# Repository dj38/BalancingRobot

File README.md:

# BalancingRobot
Balancing robot based on STM32F4 microcontroller

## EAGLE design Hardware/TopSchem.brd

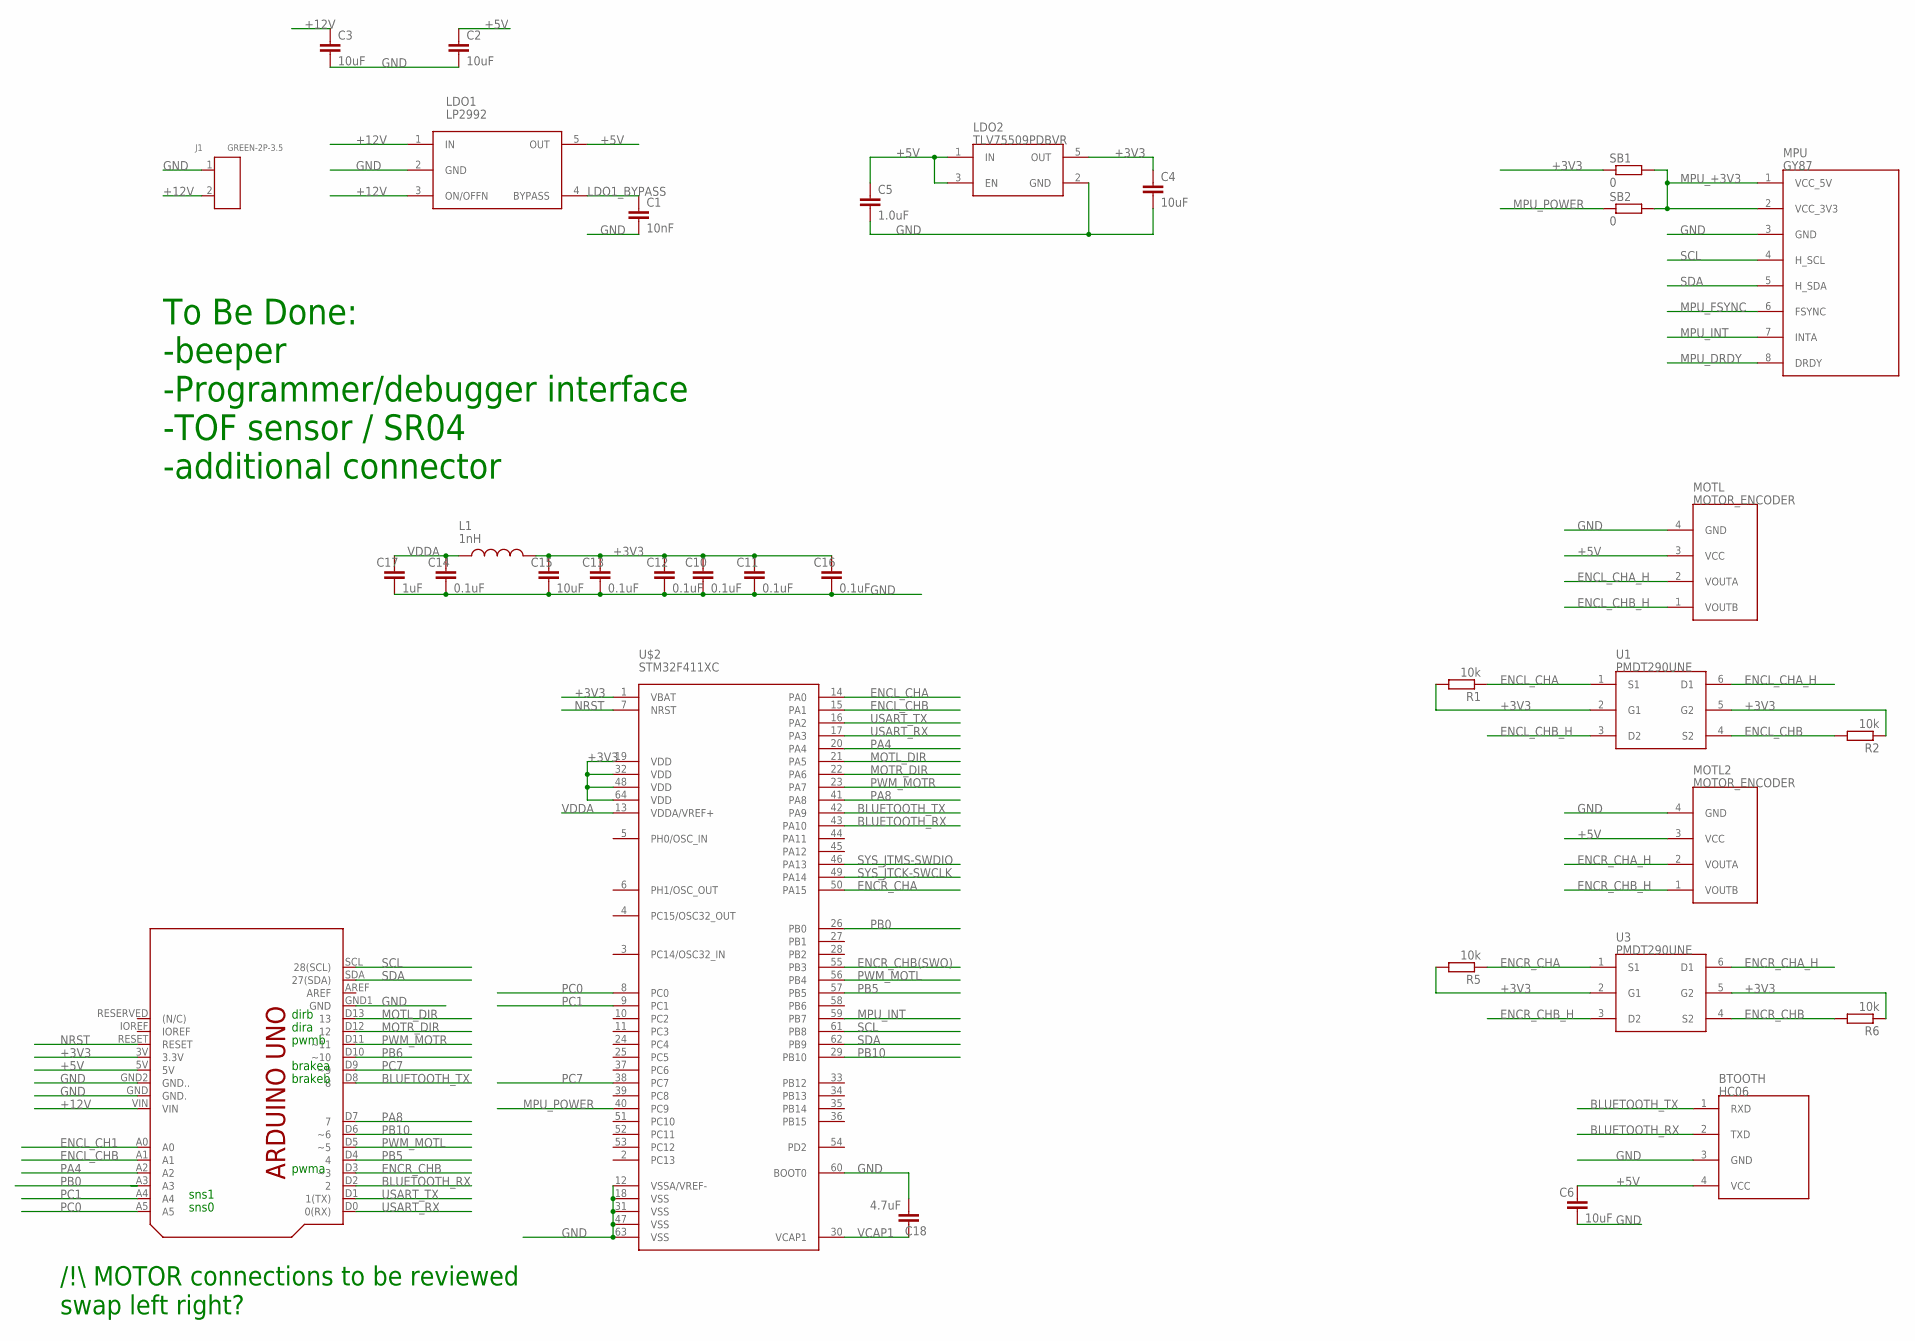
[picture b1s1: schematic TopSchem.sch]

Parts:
BTOOTH: HC06
C1: 10nF; 0603
C2, C3, C4, C6, C15: 10uF; 0603
C5: 1.0uF; 0603
C10, C11, C12, C13, C14, C16: 0.1uF; 0603
C17: 1uF; 0603
C18: 4.7uF; 0603
J1: GREEN-2P-3.5; H2-3.5-7.0X7.0MM
L1: 1nH; C0603
LDO1: LP2992; WE-TVS_SOT23-5L
LDO2: TLV75509PDBVR; WE-TVS_SOT23-5L
MOTL, MOTL2: MOTOR_ENCODER; ENCODER
MPU: GY87; SIP8
R1, R2, R5, R6: 10k; R0603
SB1, SB2: 0; R0603
SHIELD: ARDUINO_UNO_EXTARDUINO_R3; ARDUINOR3
U1, U3: PMDT290UNE; SOT666
U$2: STM32F411XC; LQFP64

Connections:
+3V3: C4.1, C10.1, C11.1, C12.1, C13.1, C15.1, C16.1, L1.2, LDO2.5 (OUT), R1.2, R2.1, R5.2, R6.1, SB1.1, SHIELD.3V (3.3V), U1.2 (G1), U1.5 (G2), U3.2 (G1), U3.5 (G2), U$2.1 (VBAT), U$2.19 (VDD), U$2.32 (VDD), U$2.48 (VDD), U$2.64 (VDD)
+5V: BTOOTH.4 (VCC), C2.1, C5.1, C6.1, LDO1.5 (OUT), LDO2.1 (IN), LDO2.3 (EN), MOTL.3 (VCC), MOTL2.3 (VCC), SHIELD.5V
+12V: C3.1, J1.2, LDO1.1 (IN), LDO1.3 (ON/OFFN), SHIELD.VIN
BLUETOOTH_RX: BTOOTH.2 (TXD), SHIELD.D2 (2), U$2.43 (PA10)
BLUETOOTH_TX: BTOOTH.1 (RXD), SHIELD.D8 (8), U$2.42 (PA9)
ENCL_CH1: SHIELD.A0
ENCL_CHA: R1.1, U1.1 (S1), U$2.14 (PA0)
ENCL_CHA_H: MOTL.2 (VOUTA), U1.6 (D1)
ENCL_CHB: R2.2, SHIELD.A1, U1.4 (S2), U$2.15 (PA1)
ENCL_CHB_H: MOTL.1 (VOUTB), U1.3 (D2)
ENCR_CHA: R5.1, U3.1 (S1), U$2.50 (PA15)
ENCR_CHA_H: MOTL2.2 (VOUTA), U3.6 (D1)
ENCR_CHB: R6.2, SHIELD.D3 (~3), U3.4 (S2)
ENCR_CHB(SWO): U$2.55 (PB3)
ENCR_CHB_H: MOTL2.1 (VOUTB), U3.3 (D2)
GND: BTOOTH.3 (GND), C1.2, C2.2, C3.2, C4.2, C5.2, C6.2, C10.2, C11.2, C12.2, C13.2, C14.2, C15.2, C16.2, C17.2, C18.2, J1.1, LDO1.2 (GND), LDO2.2 (GND), MOTL.4 (GND), MOTL2.4 (GND), MPU.3 (GND), SHIELD.GND (GND.), SHIELD.GND1 (GND), SHIELD.GND2 (GND..), U$2.12 (VSSA/VREF-), U$2.18 (VSS), U$2.31 (VSS), U$2.47 (VSS), U$2.60 (BOOT0), U$2.63 (VSS)
LDO1_BYPASS: C1.1, LDO1.4 (BYPASS)
MOTL_DIR: SHIELD.D13 (13), U$2.21 (PA5)
MOTR_DIR: SHIELD.D12 (12), U$2.22 (PA6)
MPU_+3V3: MPU.1 (VCC_5V), MPU.2 (VCC_3V3), SB1.2, SB2.2
MPU_DRDY: MPU.8 (DRDY)
MPU_FSYNC: MPU.6 (FSYNC)
MPU_INT: MPU.7 (INTA), U$2.59 (PB7)
MPU_POWER: SB2.1, U$2.40 (PC9)
NRST: SHIELD.RESET, U$2.7 (NRST)
PA4: SHIELD.A2, U$2.20 (PA4)
PA8: SHIELD.D7 (7), U$2.41 (PA8)
PB0: SHIELD.A3, U$2.26 (PB0)
PB5: SHIELD.D4 (4), U$2.57 (PB5)
PB6: SHIELD.D10 (~10)
PB10: SHIELD.D6 (~6), U$2.29 (PB10)
PC0: SHIELD.A5, U$2.8 (PC0)
PC1: SHIELD.A4, U$2.9 (PC1)
PC7: SHIELD.D9 (~9), U$2.38 (PC7)
PWM_MOTL: SHIELD.D5 (~5), U$2.56 (PB4)
PWM_MOTR: SHIELD.D11 (~11), U$2.23 (PA7)
SCL: MPU.4 (H_SCL), SHIELD.SCL (28(SCL)), U$2.61 (PB8)
SDA: MPU.5 (H_SDA), SHIELD.SDA (27(SDA)), U$2.62 (PB9)
SYS_JTCK-SWCLK: U$2.49 (PA14)
SYS_JTMS-SWDIO: U$2.46 (PA13)
USART_RX: SHIELD.D0 (0(RX)), U$2.17 (PA3)
USART_TX: SHIELD.D1 (1(TX)), U$2.16 (PA2)
VCAP1: C18.1, U$2.30 (VCAP1)
VDDA: C14.1, C17.1, L1.1, U$2.13 (VDDA/VREF+)

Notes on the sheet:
dirb
dira
pwmb
pwma
brakea
brakeb
sns1
sns0
/\!\\ MOTOR connections to be reviewed swap left right?
To Be Done: -beeper -Programmer/debugger interface -TOF sensor / SR04 -additional connector

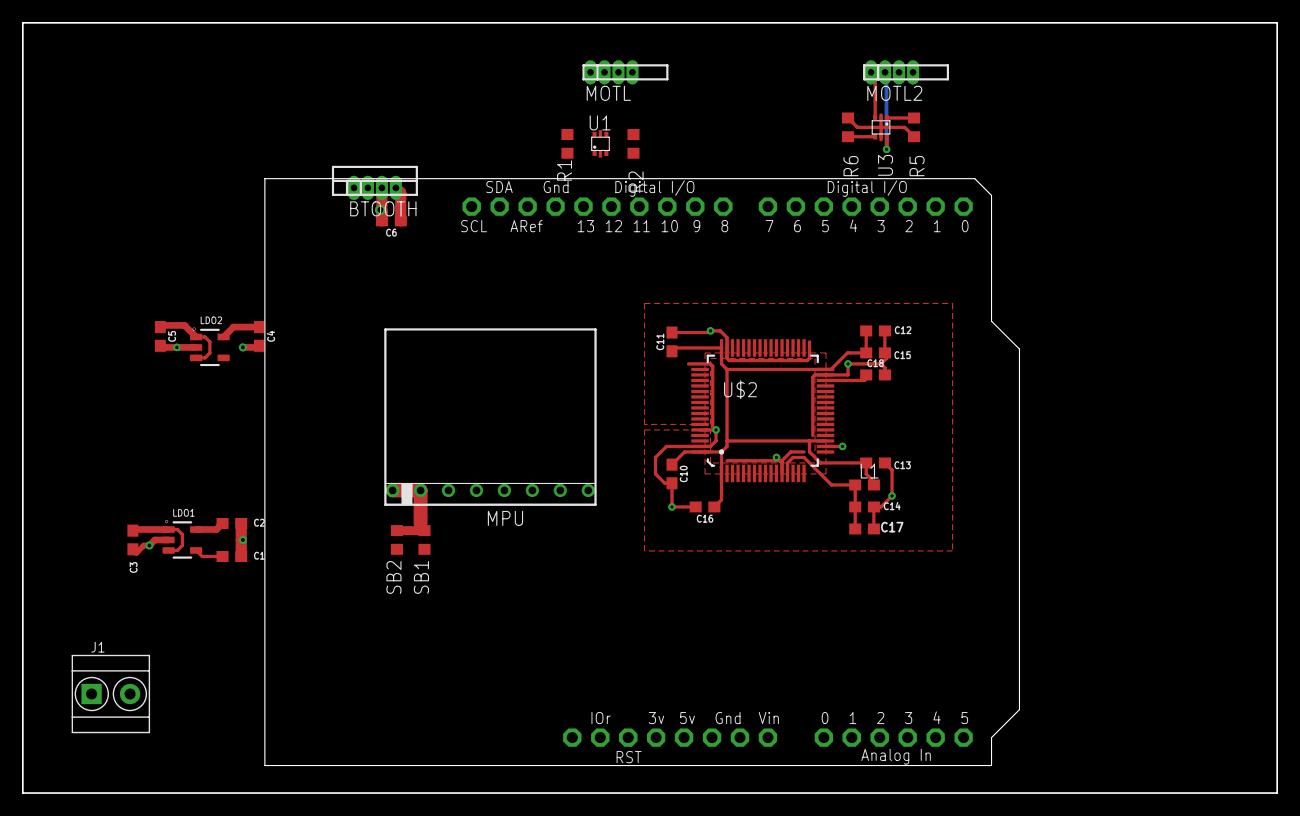
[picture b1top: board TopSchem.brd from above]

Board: 2 copper layers, 114.0 x 70.0 mm, 33 parts (0 on the bottom side), 37 nets.

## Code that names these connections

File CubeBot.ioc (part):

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Mcu.Name=STM32F411R(C-E)Tx
Mcu.Package=LQFP64
Mcu.UserName=STM32F411RETx
PA0-WKUP.GPIOParameters=GPIO_ModeDefaultPP,GPIO_Speed,GPIO_PuPd,GPIO_Label
PA0-WKUP.GPIO_Label=ENCL_CH1[TIM5_CH1]
PA0-WKUP.GPIO_ModeDefaultPP=GPIO_MODE_AF_PP
PA0-WKUP.GPIO_PuPd=GPIO_NOPULL
PA0-WKUP.GPIO_Speed=GPIO_SPEED_FREQ_LOW
PA0-WKUP.Signal=S_TIM5_CH1
PA1.GPIOParameters=GPIO_ModeDefaultPP,GPIO_Speed,GPIO_PuPd,GPIO_Label
PA1.GPIO_Label=ENCL_CH2[TIM5_CH2]
PA1.GPIO_ModeDefaultPP=GPIO_MODE_AF_PP
PA1.GPIO_PuPd=GPIO_NOPULL
PA1.GPIO_Speed=GPIO_SPEED_FREQ_LOW
PA1.Signal=S_TIM5_CH2
PA10.GPIOParameters=GPIO_Speed,GPIO_PuPd,GPIO_Label,GPIO_Mode
PA10.GPIO_Label=BLUETOOTH_RX[USART1_RX]
PA10.GPIO_Mode=GPIO_MODE_AF_PP
PA10.GPIO_PuPd=GPIO_PULLUP
PA10.GPIO_Speed=GPIO_SPEED_FREQ_VERY_HIGH
PA10.Mode=Asynchronous
PA10.Signal=USART1_RX
PA13.Signal=SYS_JTMS-SWDIO
PA14.Signal=SYS_JTCK-SWCLK
PA15.GPIOParameters=GPIO_ModeDefaultPP,GPIO_Speed,GPIO_PuPd,GPIO_Label
PA15.GPIO_Label=ENCR_CH1[TIM2_CH1]
PA15.GPIO_ModeDefaultPP=GPIO_MODE_AF_PP
PA15.GPIO_PuPd=GPIO_NOPULL
PA15.GPIO_Speed=GPIO_SPEED_FREQ_LOW
PA15.Signal=S_TIM2_CH1_ETR
PA2.GPIOParameters=GPIO_Speed,GPIO_PuPd,GPIO_Mode
PA2.GPIO_Mode=GPIO_MODE_AF_PP
PA2.GPIO_PuPd=GPIO_PULLUP
PA2.GPIO_Speed=GPIO_SPEED_FREQ_VERY_HIGH
PA2.Mode=Asynchronous
PA2.Signal=USART2_TX
PA3.GPIOParameters=GPIO_Speed,GPIO_PuPd,GPIO_Mode
PA3.GPIO_Mode=GPIO_MODE_AF_PP
PA3.GPIO_PuPd=GPIO_PULLUP
PA3.GPIO_Speed=GPIO_SPEED_FREQ_VERY_HIGH
PA3.Mode=Asynchronous
PA3.Signal=USART2_RX
PA5.GPIOParameters=GPIO_Label
PA5.GPIO_Label=MOTL_DIR[PA5]
PA5.Signal=GPIO_Output
PA6.GPIOParameters=GPIO_Label
PA6.GPIO_Label=MOTR_DIR[PA6]
PA6.Signal=GPIO_Output
PA7.GPIOParameters=GPIO_ModeDefaultPP,GPIO_Speed,GPIO_PuPd,GPIO_Label
PA7.GPIO_Label=PWM_MOTR[TIM3_CH2]
PA7.GPIO_ModeDefaultPP=GPIO_MODE_AF_PP
PA7.GPIO_PuPd=GPIO_NOPULL
PA7.GPIO_Speed=GPIO_SPEED_FREQ_LOW
PA7.Signal=S_TIM3_CH2
PA9.GPIOParameters=GPIO_Speed,GPIO_PuPd,GPIO_Label,GPIO_Mode
PA9.GPIO_Label=BLUETOOTH_TX[USART1_TX]
PA9.GPIO_Mode=GPIO_MODE_AF_PP
PA9.GPIO_PuPd=GPIO_PULLUP
PA9.GPIO_Speed=GPIO_SPEED_FREQ_VERY_HIGH
PA9.Mode=Asynchronous
PA9.Signal=USART1_TX
PB3.GPIOParameters=GPIO_ModeDefaultPP,GPIO_Speed,GPIO_PuPd,GPIO_Label
PB3.GPIO_Label=ENCR_CH2[TIM2_CH2]
PB3.GPIO_ModeDefaultPP=GPIO_MODE_AF_PP
PB3.GPIO_PuPd=GPIO_NOPULL
PB3.GPIO_Speed=GPIO_SPEED_FREQ_LOW
PB3.Signal=S_TIM2_CH2
PB4.GPIOParameters=GPIO_ModeDefaultPP,GPIO_Speed,GPIO_PuPd,GPIO_Label
PB4.GPIO_Label=PWM_MOTL[TIM3_CH1]
PB4.GPIO_ModeDefaultPP=GPIO_MODE_AF_PP
PB4.GPIO_PuPd=GPIO_NOPULL
PB4.GPIO_Speed=GPIO_SPEED_FREQ_LOW
PB4.Signal=S_TIM3_CH1
PB7.GPIOParameters=GPIO_PuPd,GPIO_Label
PB7.GPIO_Label=MPU_INT
PB7.GPIO_PuPd=GPIO_NOPULL
PB7.Signal=GPIO_Input
PB8.GPIOParameters=GPIO_Speed,GPIO_PuPdOD,GPIO_Mode
PB8.GPIO_Mode=GPIO_MODE_AF_OD
PB8.GPIO_PuPdOD=GPIO_PULLUP
PB8.GPIO_Speed=GPIO_SPEED_FREQ_VERY_HIGH
PB8.Mode=I2C
PB8.Signal=I2C1_SCL
PB9.GPIOParameters=GPIO_Speed,GPIO_PuPdOD,GPIO_Mode
PB9.GPIO_Mode=GPIO_MODE_AF_OD
PB9.GPIO_PuPdOD=GPIO_PULLUP
PB9.GPIO_Speed=GPIO_SPEED_FREQ_VERY_HIGH
PB9.Mode=I2C
PB9.Signal=I2C1_SDA
PC13-ANTI_TAMP.GPIOParameters=GPIO_PuPd,GPIO_ModeDefaultEXTI
PC13-ANTI_TAMP.GPIO_ModeDefaultEXTI=GPIO_MODE_IT_RISING
PC13-ANTI_TAMP.GPIO_PuPd=GPIO_NOPULL
PC13-ANTI_TAMP.Signal=GPXTI13
PC14-OSC32_IN.Signal=RCC_OSC32_IN
PC15-OSC32_OUT.Signal=RCC_OSC32_OUT
PC9.GPIOParameters=GPIO_Speed,PinState,GPIO_Label
PC9.GPIO_Label=MPU_POWER
PC9.GPIO_Speed=GPIO_SPEED_FREQ_HIGH
PC9.PinState=GPIO_PIN_RESET
PC9.Signal=GPIO_Output
PH0\ -\ OSC_IN.Signal=RCC_OSC_IN
PH1\ -\ OSC_OUT.Signal=RCC_OSC_OUT
RCC.HSE_VALUE=8000000
RCC.SYSCLKFreq_VALUE=100000000
RCC.SYSCLKSource=RCC_SYSCLKSOURCE_PLLCLK
board=NUCLEO-F411RE
boardIOC=true

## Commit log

2018-01-20 First commit to test env
2018-01-20 import all project files on repo.
2018-01-20 Use of pid_T to store measure/target on speed and angle.
2018-01-20 theta variables renamed azimut
2018-01-20 Added getPreviousTime function.
2018-01-22 Added communication commands to handle azimut regulation.
2018-01-23 Added turnToAngle command support in communication.
2018-02-07 Print float without ostringstream buffer. Added following C Linker options : -u _scanf_float -u _printf_float
2018-02-08 Added Release config to gitignore
2018-02-08 Main update to reactivate regulation.
2018-02-08 Begining implementation of azimuth regulation.
2018-02-08 Project config update: -to allow printf on float -to reduce code size (C/C++ reduced)
2018-02-08 Project setup update
2018-02-09 Removed includes of sstream and iostream to reduce code size. 200kb => 65kb
2018-02-09 Updated project config.
2018-02-13 SerialBuffer and BTCom updated to allow copy and affectations of those classes. (using a shared representation of the SerialBuffer Class)
2018-02-13 Removing lines used to validate float print and copy of serialBuffers.
2018-02-15 Serial Buffer renamed IOSerialStream.
2018-02-19 IOStreamList introduced and functional. Based on an abstract Class IOStream.
2018-02-21 Template function is functional for IOStream::operator<<. (Not possible to split delaration and definition... export keyword not supported by compilator)
2018-02-21 write private functions for uint8/16/32 removed as unused.
2018-02-21 Enable feature added on StreamList.
2018-02-21 MPU6050 is derived from streamList for debug.
2018-02-21 StatLog updated to use IOStreamList instead of IOSerialStream. (Print on several serials)
2018-04-17 Using IOStreamList to display Hello World.
2018-10-07 Squashed commit of the following: Implementation of EEPROM emulation using 2 FLASH PAGES. Allows to save PID variables to EEPROM. UART communication commands updated accordingly. New commands : -FEE 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
    commit 76ee166f919603567bf13266d956a8a551de70cd
    Author: joel <joel.damiens@laposte.net>
    Date: Sat Oct 06 22:10:15 2018 +0200
    Implementation of format EEPROM uart command.
    commit 8488448ffab3dba087941d8ffa9a87082dfbb5b4
    Author: joel <joel.damiens@laposte.net>
2018-10-20 .gitignore update to avoid tracking modif in .settings folder
2018-10-20 Enable display of position/angle/speed
2018-10-20 Fixed error in branch merge.
2018-10-20 Modified .gitignore to avoid to track changes in .settings folder
2018-10-22 Re-enable Statlogs that had been disabled a long time ago for debug.
2018-10-22 INT pin is used to trigger a MPU6050 data reading. Re enable statlogs on MPU6050. CubeMX project update to add MPU_INT pin. Added MPU6050 docs in project.
2018-10-22 A global and and a loop timers are added. Global monitors overall runtime loopTimer monitors elapsed time in main loop. Time consuming display are not allowed in loopTimer is above a given threshold.
2019-04-18 Adding motor doc
2020-09-30 Adding STM32 docs.
2020-09-30 Project migration to STM32CubeIDE v1.4.0
2020-11-09 adding Hardware folder for PCB development with Eagle

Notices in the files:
parts and their libraries:
SparkFun-Capacitors: Licensing: Creative Commons ShareAlike 4.0 International - https://creativecommons.org/licenses/by-sa/4.0
